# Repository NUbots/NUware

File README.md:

# NUware
Hardware used by the NUbots team.

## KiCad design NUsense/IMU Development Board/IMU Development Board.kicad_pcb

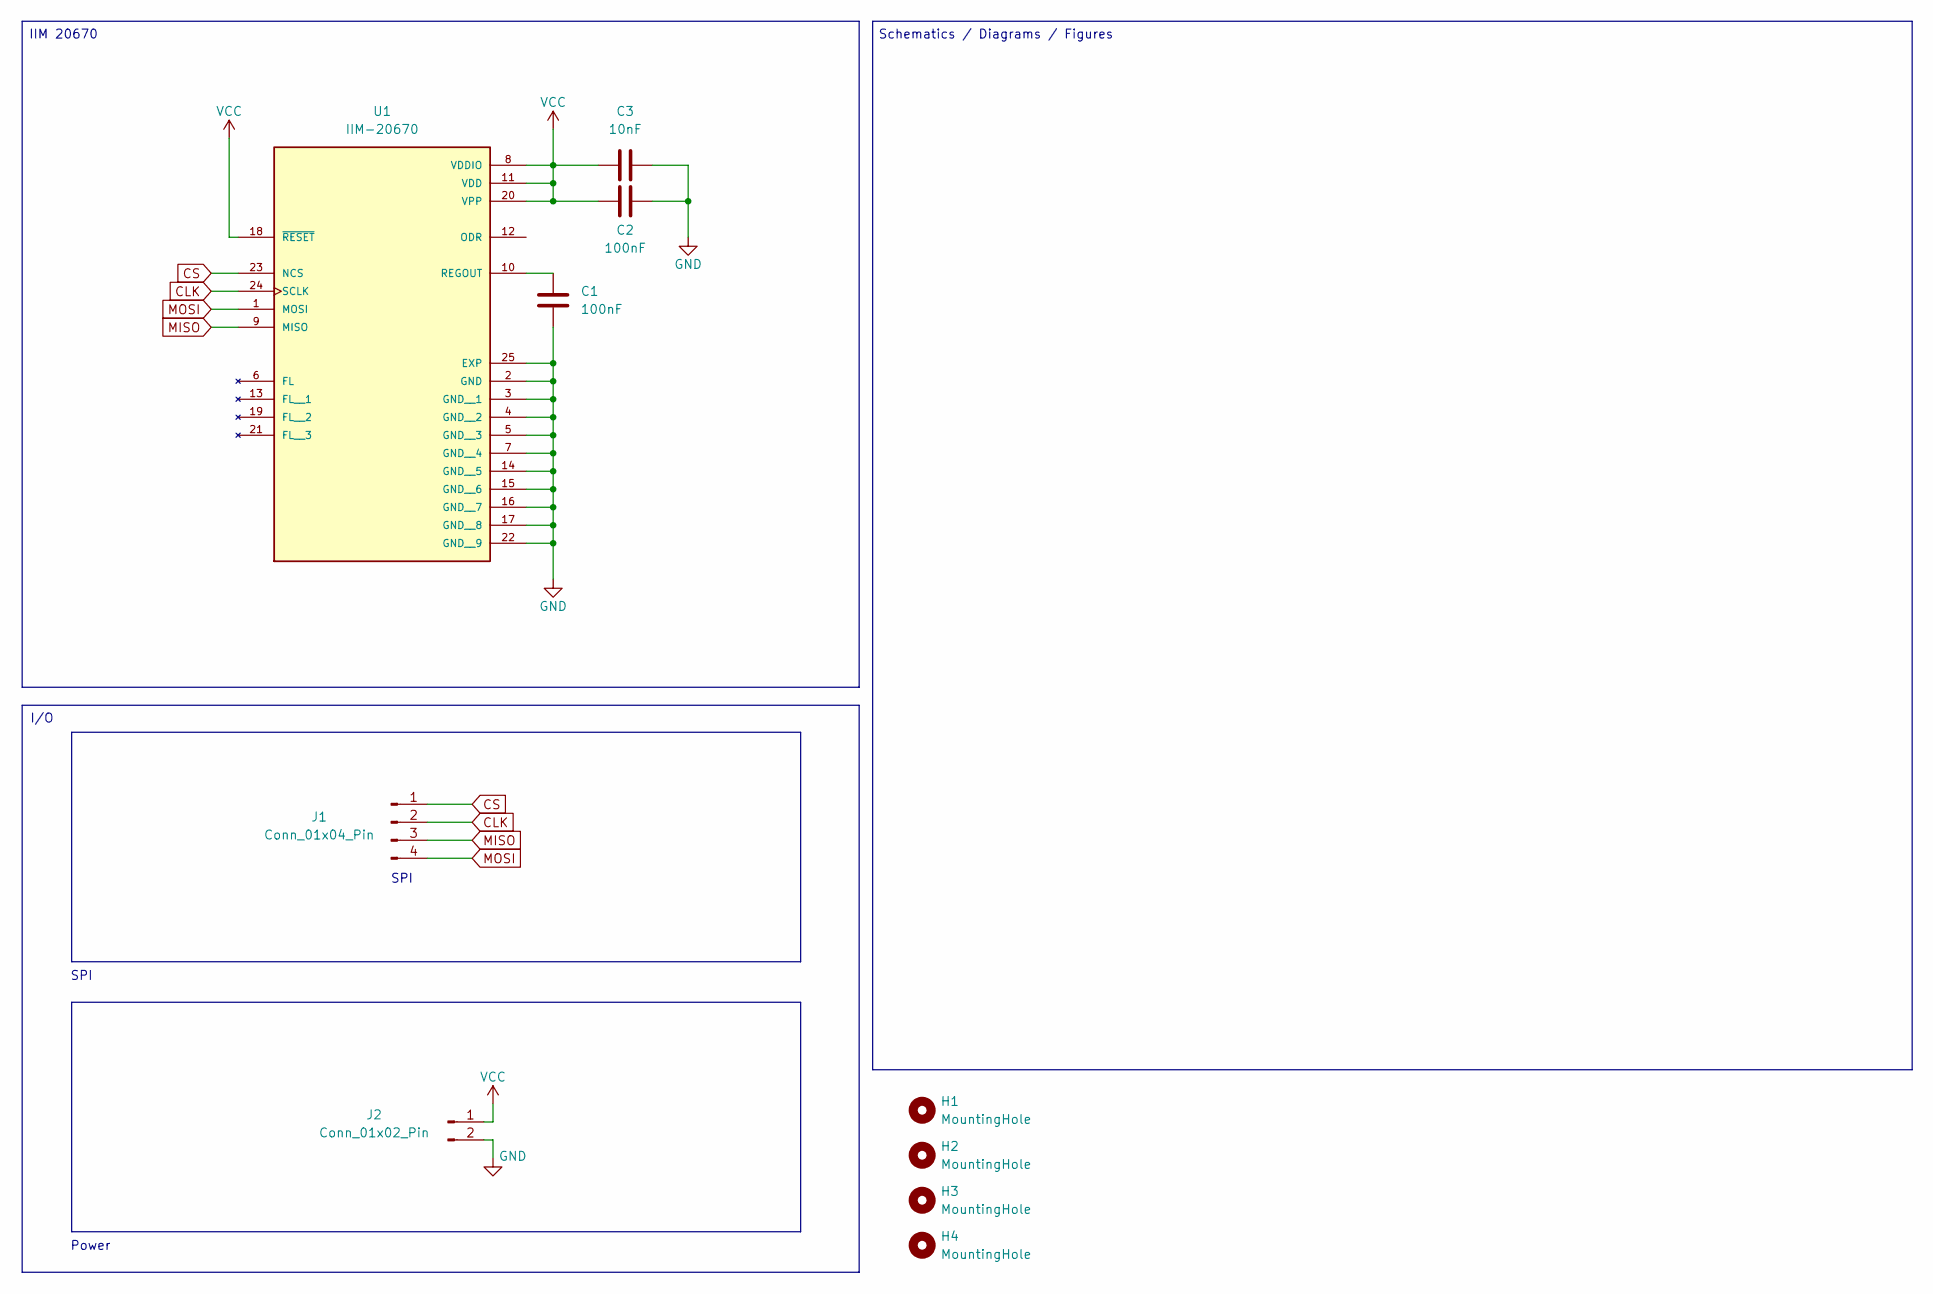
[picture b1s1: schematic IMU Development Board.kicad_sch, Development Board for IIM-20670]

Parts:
C1, C2: 100nF; C_1808_4520Metric_Pad1.72x2.30mm_HandSolder
C3: 10nF; C_1808_4520Metric_Pad1.72x2.30mm_HandSolder
H1, H2, H3, H4: MountingHole; MountingHole_4mm
J1: Conn_01x04_Pin; PinHeader_1x04_P2.54mm_Vertical_SMD_Pin1Left
J2: Conn_01x02_Pin; PinHeader_1x02_P2.54mm_Vertical_SMD_Pin1Left
U1: IIM-20670; QFN50P450X450X115-25N; PARTREV 1.1

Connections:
CLK: J1.2, U1.24 (SCLK)
CS: J1.1, U1.23 (NCS)
GND: C1.2, C2.1, C3.2, J2.2, U1.2 (GND), U1.3 (GND__1), U1.4 (GND__2), U1.5 (GND__3), U1.7 (GND__4), U1.14 (GND__5), U1.15 (GND__6), U1.16 (GND__7), U1.17 (GND__8), U1.22 (GND__9), U1.25 (EXP)
MISO: J1.3, U1.9 (MISO)
MOSI: J1.4, U1.1 (MOSI)
unnamed: C1.1, U1.10 (REGOUT)
VCC: C2.2, C3.1, J2.1, U1.8 (VDDIO), U1.11 (VDD), U1.18 (~RESET), U1.20 (VPP)

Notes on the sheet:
Power
IIM 20670
Schematics / Diagrams / Figures
I/O
SPI

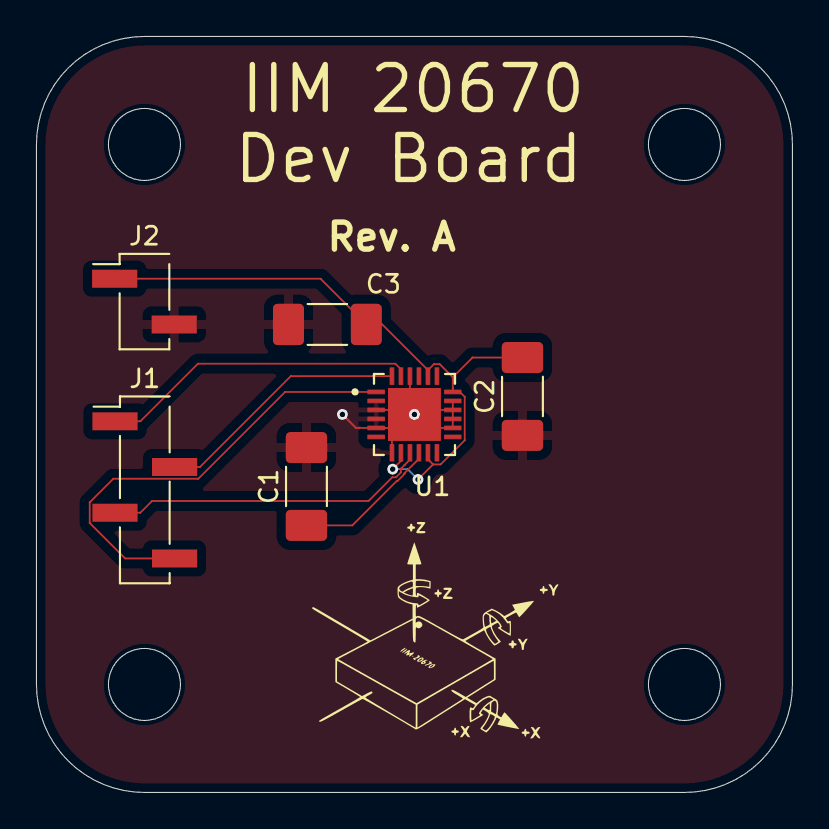
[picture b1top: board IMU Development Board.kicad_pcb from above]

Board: 2 copper layers, 42.0 x 42.0 mm, 10 parts (0 on the bottom side), 7 nets.

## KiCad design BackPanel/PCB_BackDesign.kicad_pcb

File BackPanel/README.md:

Back-Panel IO
=============

## Brief
Displays information through a series of LEDs including two RGB LEDs and takes inputs in from the user through three buttons; one of which shuts of power to the servos in case of an emergency. As a further convenience, there are two headers to power two fans with 12 V. The PCB is connected to the subcontroller through two cables.

## Motivation
The back-panel IO [originally designed by Robotis](https://github.com/ROBOTIS-GIT/ROBOTIS-OP-Series-Data/blob/master/ROBOTIS-OP%2C%20ROBOTIS-OP2/Hardware/Electronics/Boards/DARwIn-OP_Interface_rev3.pdf) was modified slightly for the NUgus to have 3D-printed buttons. These buttons floated between the PCB and the outer panel. As such, they were very finicky and sometimes got themselves stuck. Furthermore, given that the underlying electrical switch was a generic tactile momentary switch with a very short actuation depth, there was little tactile feedback. That is to say that there wasn't a very satsifying click which sometimes made the user doubt whether a contact was made. (This would compound separate but related issues with the reliability of the button firmware.) Another grievance was the fact that the mounting holes of the PCB were near the pads of the switches; if a metal washer was used, then it would short the switch.

## Resistors
The original design by Robotis had only 470 Ω resistors for all LEDs including the RGB ones. This seemed inconsistent; so, 240 Ω resistors were used for the green and blue LEDs since they often have higher forward voltages. Going off from [the datasheet](https://s3-us-west-2.amazonaws.com/catsy.557/Dialight_CBI_data_598-0603_Apr2018.pdf) for the Dialight 598 series, these resistors should give a current of 2.5 mA in each LED and roughly a forward voltage of 2 V for the red and yellow-green LEDs, 2.6 V for the blue LED, and 2.75 V for the green LED.

## Switch
[The KS11R2xCQD](https://www.ckswitches.com/media/1342/ks.pdf) was chosen as the replacement switch since it had a longer travel of 0.71 mm, had shorter profile than similar alternatives, and was relatively cheaper.

An alternative for future revisions is [the 5501M series](https://sten-eswitch-13110800-production.s3.amazonaws.com/system/asset/product_line/data_sheet/24/5500.pdf) which has a longer travel of about 1 mm -- the datasheet is somewhat ambiguous. It can even have an embedded LED which can be wired to the second arm of a SPDT -- labelled NC in the datasheet -- and can be used to signify when the button is pressed as a form of visual feedback. However, compared to the KS11R2xCQD, it has a much taller profile which would mean that the PCB would need to be recessed further back into the torso.

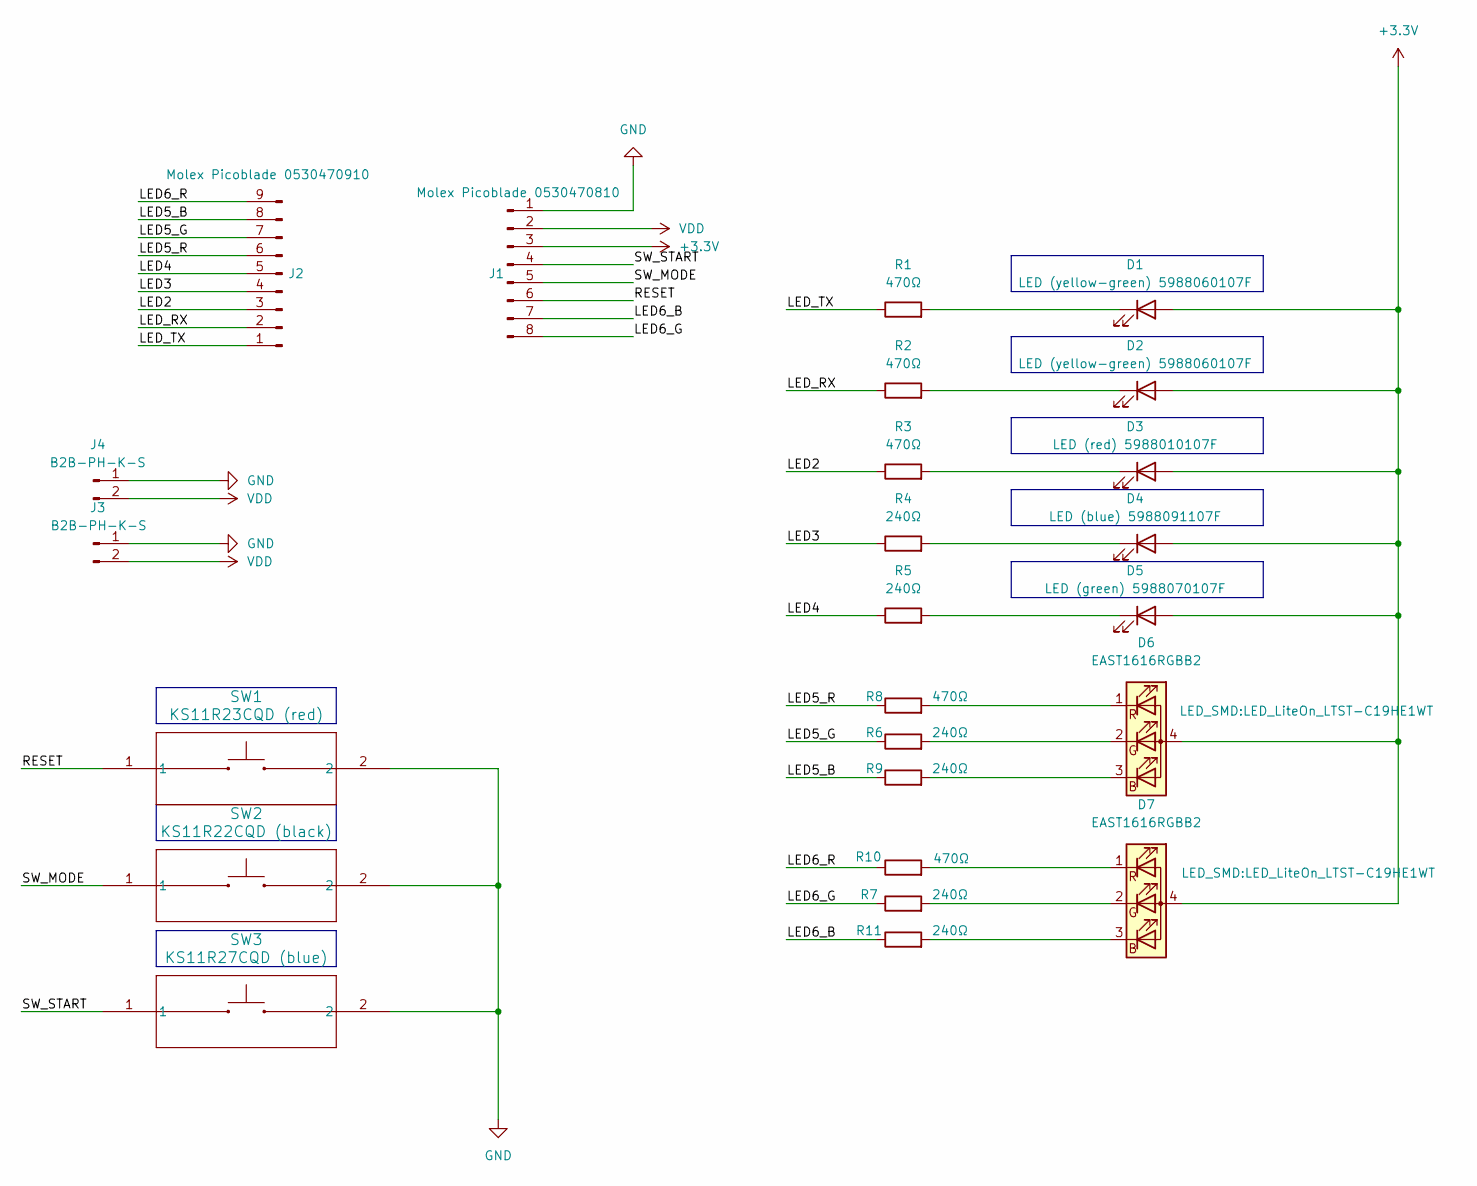
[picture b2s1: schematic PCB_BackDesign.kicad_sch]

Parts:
D1, D2: LED (yellow-green) 5988060107F; LED_0603_1608Metric
D3: LED (red) 5988010107F; LED_0603_1608Metric
D4: LED (blue) 5988091107F; LED_0603_1608Metric
D5: LED (green) 5988070107F; LED_0603_1608Metric
D6, D7: EAST1616RGBB2; LED_LiteOn_LTST-C19HE1WT
J1: Molex Picoblade 0530470810; Molex_PicoBlade_53047-0810_1x08_P1.25mm_Vertical
J2: Molex Picoblade 0530470910; Molex_PicoBlade_53047-0910_1x09_P1.25mm_Vertical
J3, J4: B2B-PH-K-S; JST_PH_B2B-PH-K_1x02_P2.00mm_Vertical
R1, R2, R3, R8, R10: 470Ω; R_0603_1608Metric
R4, R5, R6, R7, R9, R11: 240Ω; R_0603_1608Metric
SW1: KS11R23CQD (red); KS11_CNK
SW2: KS11R22CQD (black); KS11_CNK
SW3: KS11R27CQD (blue); KS11_CNK

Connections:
+3.3V: D1.2 (A), D2.2 (A), D3.2 (A), D4.2 (A), D5.2 (A), D6.4 (A), D7.4 (A), J1.3
/LED2: J2.3, R3.1
/LED3: J2.4, R4.1
/LED4: J2.5, R5.1
/LED5_B: J2.8, R9.1
/LED5_G: J2.7, R6.1
/LED5_R: J2.6, R8.1
/LED6_B: J1.7, R11.1
/LED6_G: J1.8, R7.1
/LED6_R: J2.9, R10.1
/LED_RX: J2.2, R2.1
/LED_TX: J2.1, R1.1
/RESET: J1.6, SW1.1; also elsewhere on the board
/SW_MODE: J1.5, SW2.1; also elsewhere on the board
/SW_START: J1.4, SW3.1; also elsewhere on the board
GND: J1.1, J3.1, J4.1, SW1.2, SW2.2, SW3.2; also elsewhere on the board
unnamed: D1.1 (K), R1.2
unnamed: D2.1 (K), R2.2
unnamed: D3.1 (K), R3.2
unnamed: D4.1 (K), R4.2
unnamed: D5.1 (K), R5.2
unnamed: D6.3 (BK), R9.2
unnamed: D6.2 (GK), R6.2
unnamed: D6.1 (RK), R8.2
unnamed: D7.3 (BK), R11.2
unnamed: D7.2 (GK), R7.2
unnamed: D7.1 (RK), R10.2
VDD: J1.2, J3.2, J4.2

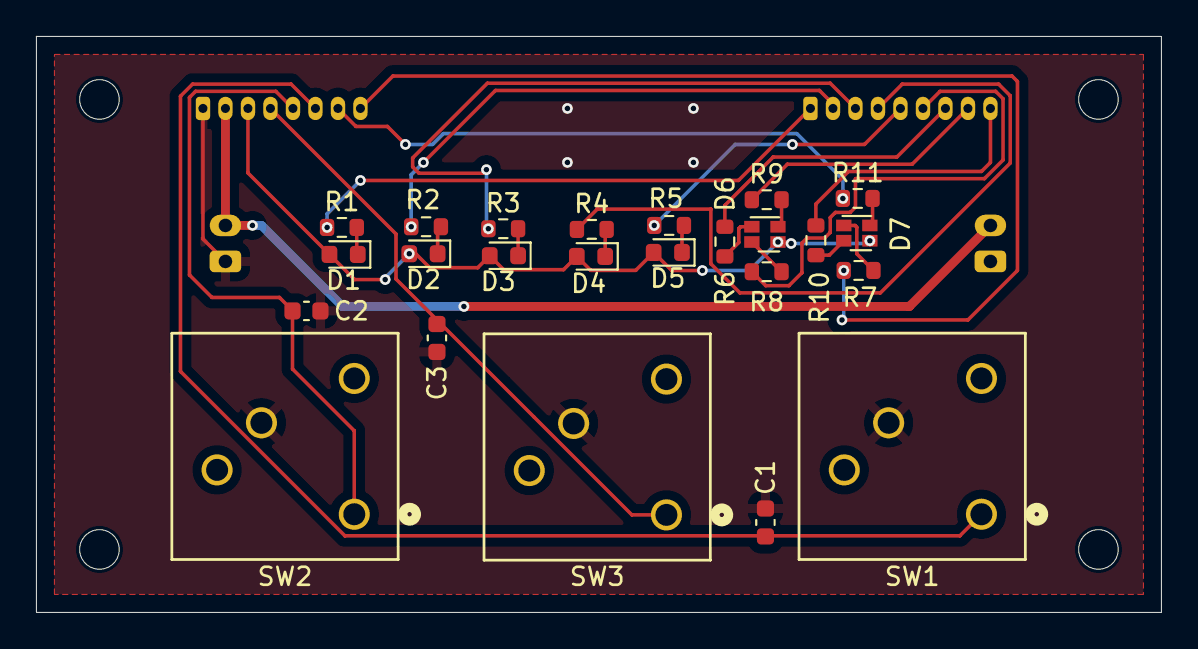
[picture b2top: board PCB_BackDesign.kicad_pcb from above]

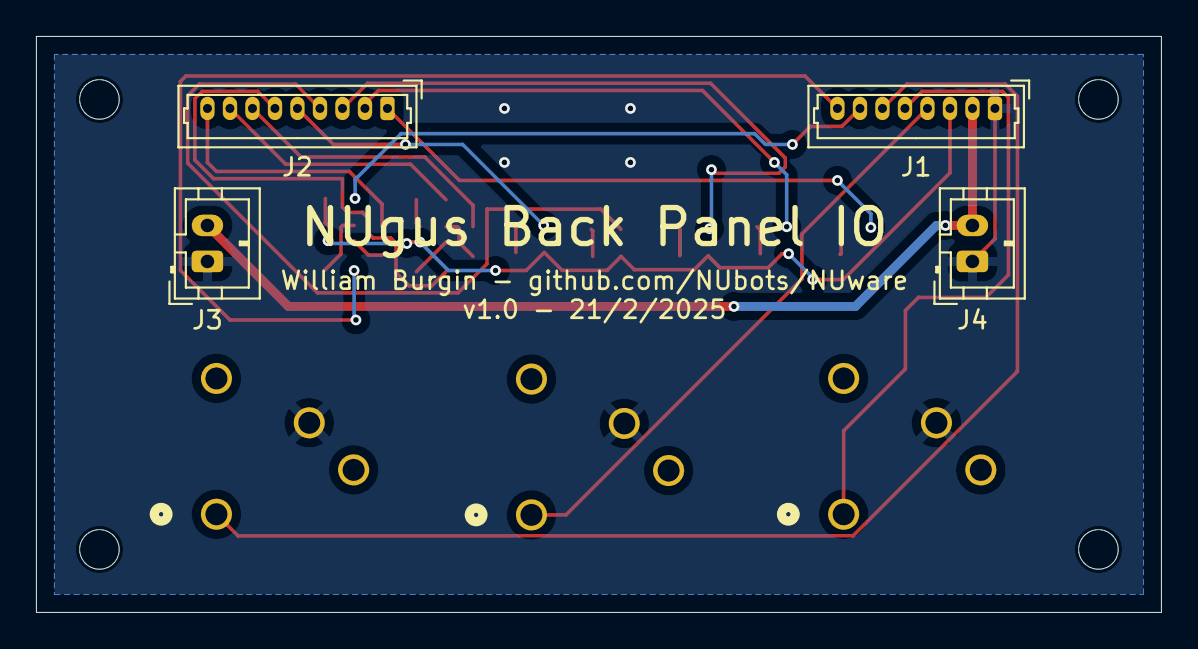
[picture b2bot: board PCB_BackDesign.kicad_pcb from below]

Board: 2 copper layers, 62.5 x 32.0 mm, 28 parts (4 on the bottom side), 28 nets.

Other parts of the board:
C1, C2, C3: 100nF; C_0603_1608Metric

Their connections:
/RESET: C1.1; also elsewhere on the board
/SW_MODE: C2.1; also elsewhere on the board
/SW_START: C3.1; also elsewhere on the board
GND: C1.2, C2.2, C3.2; also elsewhere on the board

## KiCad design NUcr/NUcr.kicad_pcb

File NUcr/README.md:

NUcr
====

## Motivation
The bare OpenCR 1.0 board did not have enough headers nor the right headers for the then existing cabling that was used for the CM740. For example, the OpenCR only has three JST B4B-EH-A headers for the RS485 Dynamixel bus.

## Description
This Arduino-like shield effectively emulated the headers found on the CM740 as well as a few other conveniences like a connection for a standalone RS485 serial converter and headers for 12 V fans.

It has:
* nine Molex Spox 22-03-5045 headers -- three of which connect to the OpenCR's three JST headers --,
* one Molex Picoblade 53047-0810 header and one 53047-0910 header for the button panel,
* four JST B2B-PH-K-S headers for the fans -- one of which connects to the OpenCR's 12 V header --,
* an Arduino footprint -- this only serves to connect 3.3 V and to provide structural connection --,
* and lastly one three-pin header for a standalone RS485 serial converter.

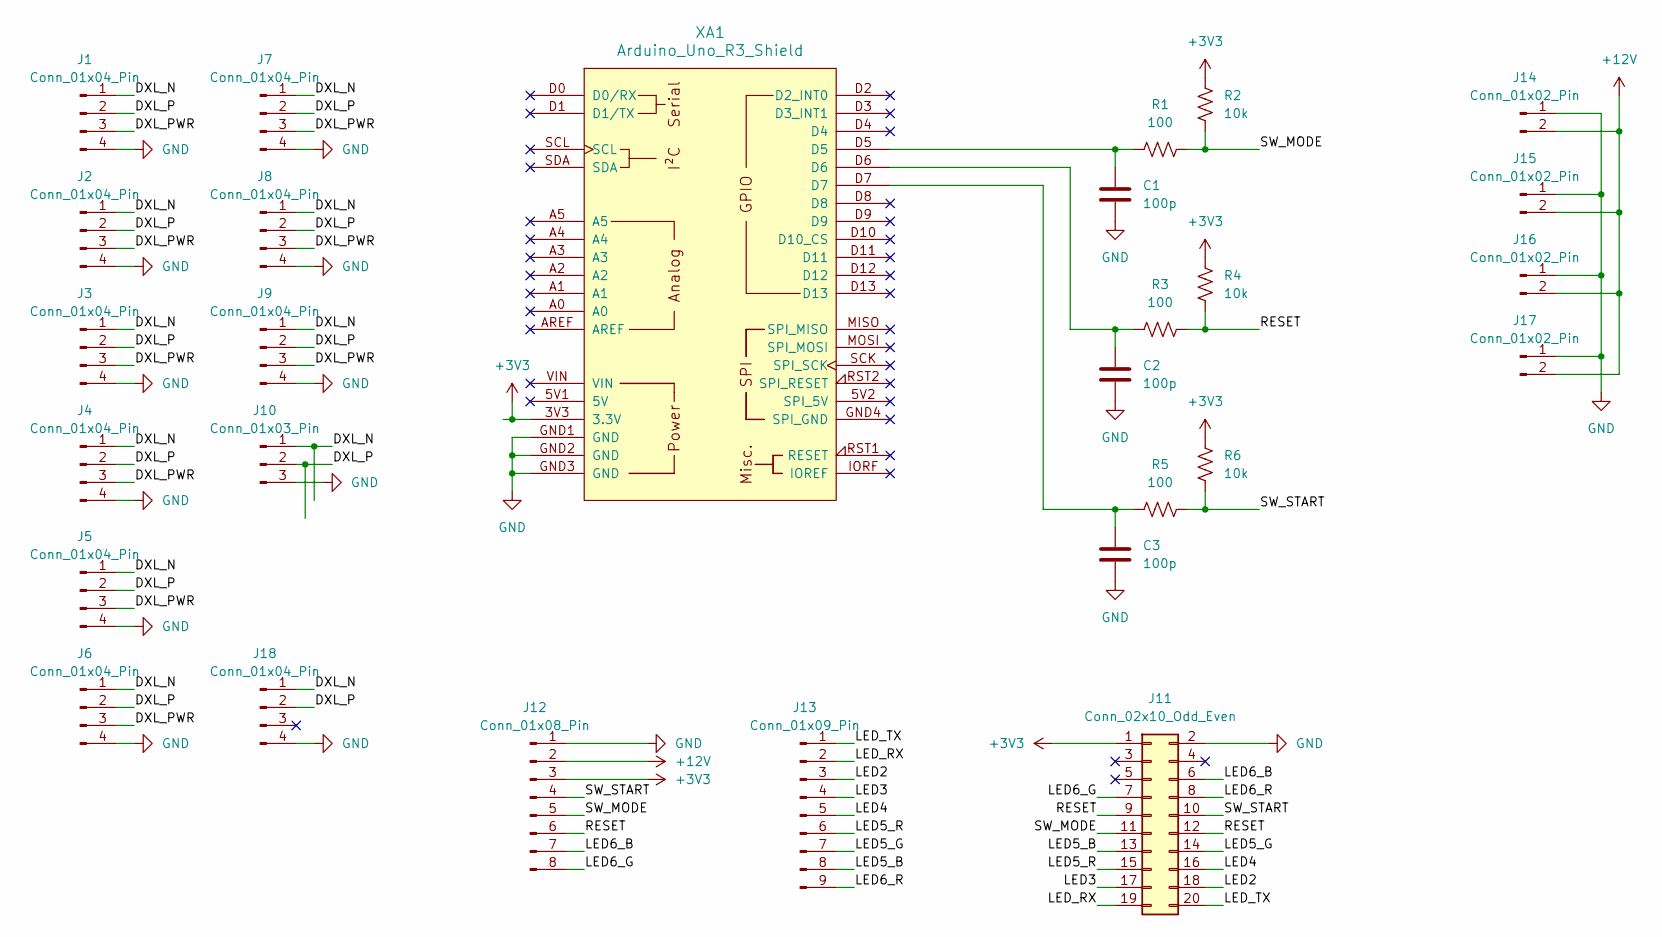
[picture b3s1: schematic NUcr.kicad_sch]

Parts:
C1, C2, C3: 100p; C_0603_1608Metric
J1, J2, J3, J4, J5, J6, J7, J8, J9: Conn_01x04_Pin; Molex_SPOX_5267-04A_1x04_P2.50mm_Vertical
J10: Conn_01x03_Pin; PinHeader_1x03_P2.54mm_Vertical
J11: Conn_02x10_Odd_Even; PinSocket_2x10_P2.54mm_Vertical
J12: Conn_01x08_Pin; Molex_PicoBlade_53047-0810_1x08_P1.25mm_Vertical
J13: Conn_01x09_Pin; Molex_PicoBlade_53047-0910_1x09_P1.25mm_Vertical
J14, J15, J16, J17: Conn_01x02_Pin; JST_PH_B2B-PH-K_1x02_P2.00mm_Vertical
J18: Conn_01x04_Pin; PinHeader_1x04_P2.54mm_Vertical
R1, R3, R5: 100; R_0603_1608Metric
R2, R4, R6: 10k; R_0603_1608Metric
XA1: Arduino_Uno_R3_Shield

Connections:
+3V3: J11.1, J12.3, R2.1, R4.1, R6.1, XA1.3V3 (3.3V)
+12V: J12.2, J14.2, J15.2, J16.2, J17.2
/DXL_N: J1.1, J2.1, J3.1, J4.1, J5.1, J6.1, J7.1, J8.1, J9.1, J10.1, J18.1
/DXL_P: J1.2, J2.2, J3.2, J4.2, J5.2, J6.2, J7.2, J8.2, J9.2, J10.2, J18.2
/DXL_PWR: J1.3, J2.3, J3.3, J4.3, J5.3, J6.3, J7.3, J8.3, J9.3
/LED2: J11.18, J13.3
/LED3: J11.17, J13.4
/LED4: J11.16, J13.5
/LED5_B: J11.13, J13.8
/LED5_G: J11.14, J13.7
/LED5_R: J11.15, J13.6
/LED6_B: J11.6, J12.7
/LED6_G: J11.7, J12.8
/LED6_R: J11.8, J13.9
/LED_RX: J11.19, J13.2
/LED_TX: J11.20, J13.1
/RESET: J11.9, J11.12, J12.6, R3.2, R4.2
/SW_MODE: J11.11, J12.5, R1.2, R2.2
/SW_START: J11.10, J12.4, R5.2, R6.2
GND: C1.2, C2.2, C3.2, J1.4, J2.4, J3.4, J4.4, J5.4, J6.4, J7.4, J8.4, J9.4, J10.3, J11.2, J12.1, J14.1, J15.1, J16.1, J17.1, J18.4, XA1.GND1 (GND), XA1.GND2 (GND), XA1.GND3 (GND)
unnamed: C1.1, R1.1, XA1.D5
unnamed: C2.1, R3.1, XA1.D6
unnamed: C3.1, R5.1, XA1.D7

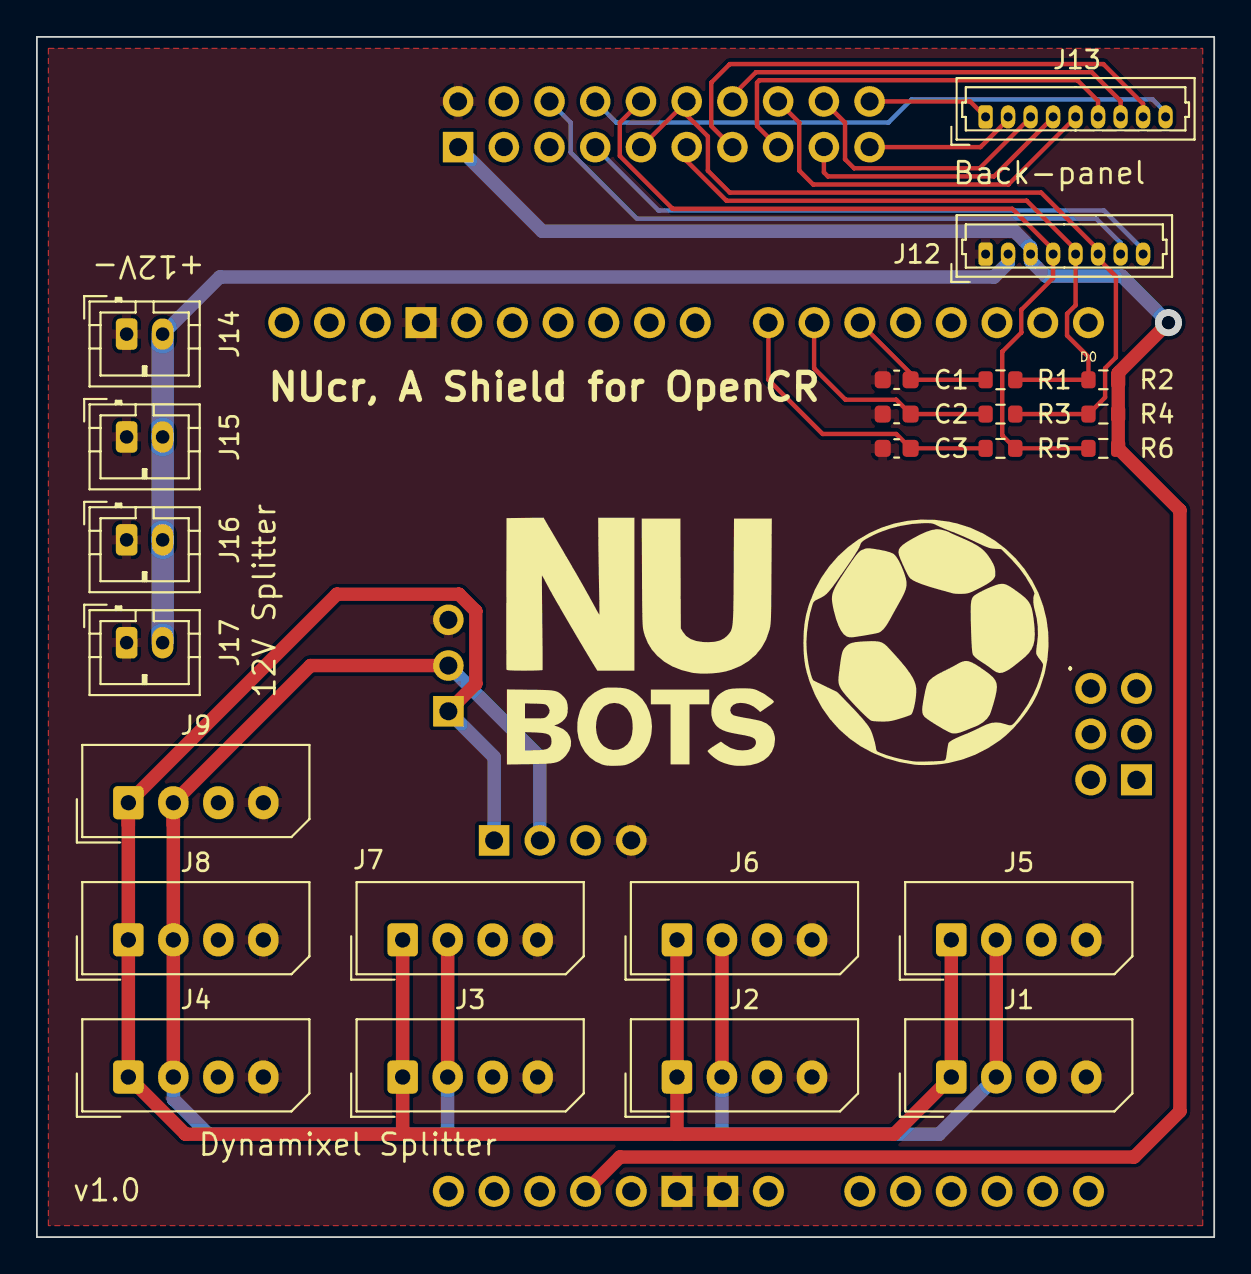
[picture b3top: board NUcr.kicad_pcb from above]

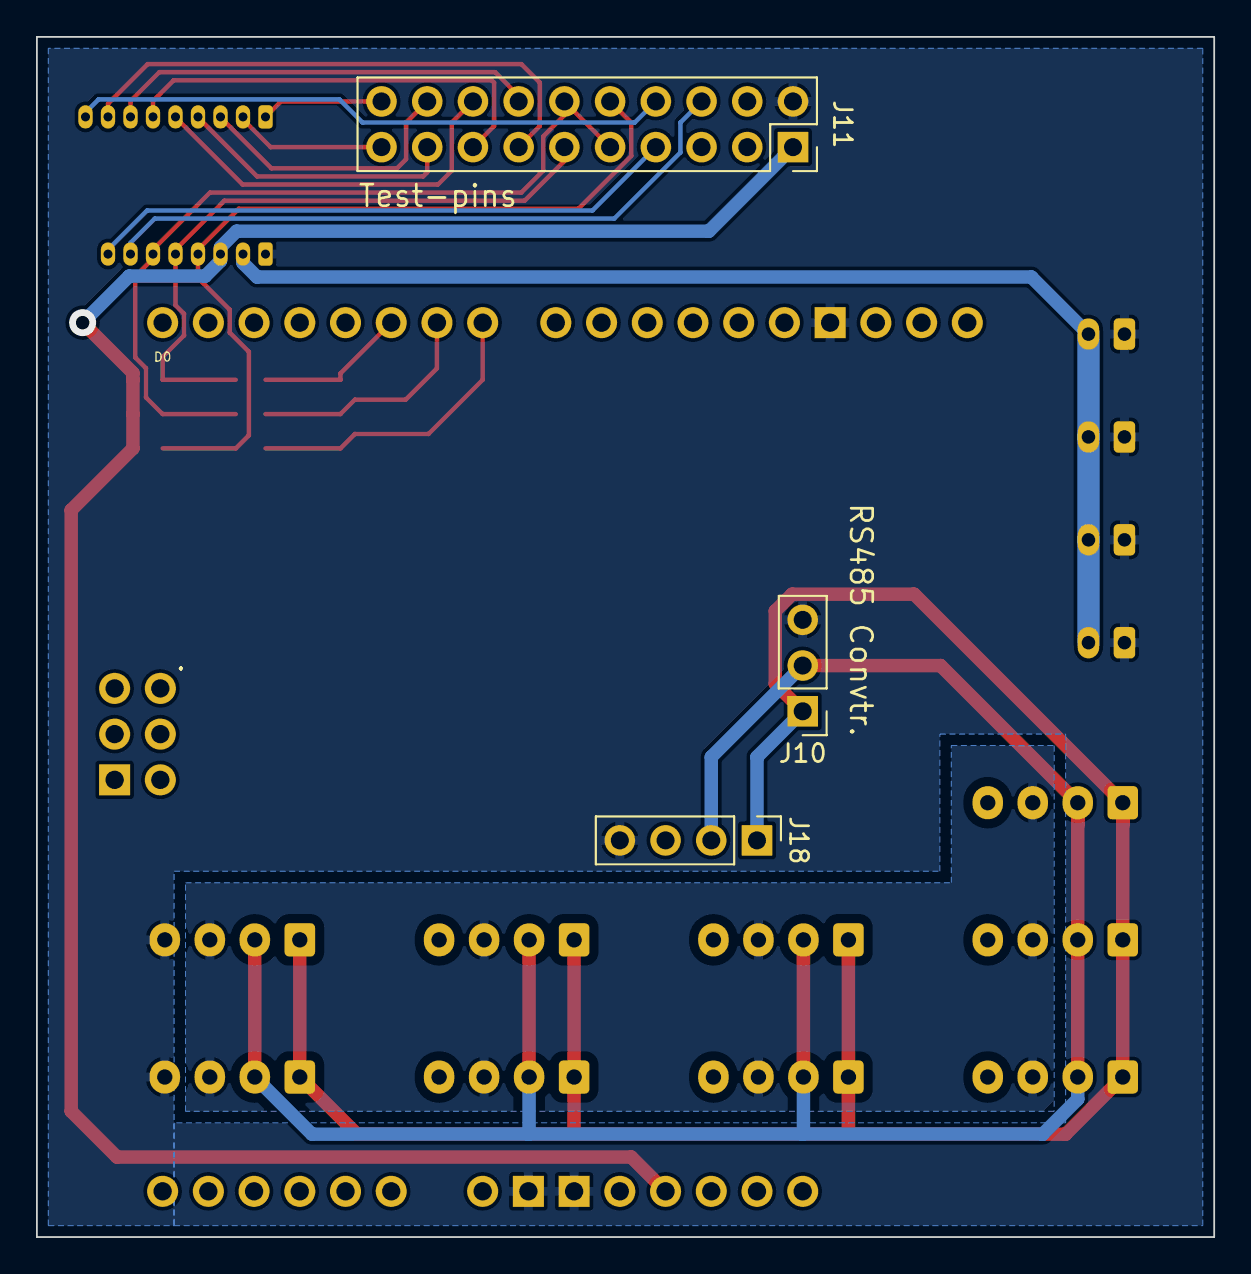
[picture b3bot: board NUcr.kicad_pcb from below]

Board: 2 copper layers, 65.4 x 66.7 mm, 28 parts (3 on the bottom side), 23 nets.

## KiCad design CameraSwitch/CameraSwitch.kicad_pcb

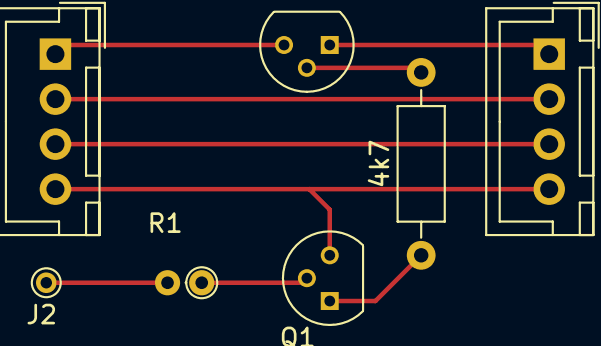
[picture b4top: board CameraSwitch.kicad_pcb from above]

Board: 2 copper layers, 7 parts (0 on the bottom side), 9 nets.

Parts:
4k7: R2; R_Axial_DIN0207_L6.3mm_D2.5mm_P10.16mm_Horizontal
J1: USB_IN; JST_XH_B04B-XH-A_04x2.50mm_Straight
J2: GPIO; PINTST
J3: USB_OUT; JST_XH_B04B-XH-A_04x2.50mm_Straight
Q1: BC547; TO-92_Molded_Narrow
Q2: BC327; TO-92_Molded_Narrow
R1: 10k; R_Axial_DIN0204_L3.6mm_D1.6mm_P1.90mm_Vertical

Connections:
/3V3: J2.1, R1.2
/5V_IN: J1.1, Q2.3
/5V_OUT: J3.1, Q2.1
/D+: J1.2, J3.2
/D-: J1.3, J3.3
Earth: J1.4, J3.4, Q1.3
unnamed: 4k7.1, Q1.1
unnamed: 4k7.2, Q2.2
unnamed: Q1.2, R1.1

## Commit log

2017-06-02 Cleans up formatting in README.md.
2017-06-02 Adds the USB Camera Switch kicad design files.
2017-06-02 Adds the Power Board altium design files.
2017-06-25 Igus design files
2017-06-26 Rearranged files and added a readme for the igus files.
2017-07-19 Adds license
2018-01-25 Create A
2018-01-29 Update NUsense Files
2018-01-30 Ignore backup files
2018-01-30 Change hierarchy layout
2018-01-30 Add power components
2018-01-30 Update Component Values
2018-01-31 Correct broken files
2018-01-31 Add files
2018-01-31 Adds datasheets
2018-01-31 Main page additions
2018-01-31 Add datasheet
2018-01-31 Add datasheets
2018-01-31 Update connections
2018-02-01 Footprints
2018-02-01 ESD protection
2018-02-02 Adds new schematic symbols
    AVRC5S and DXL_PWR
2018-02-02 Adds more datasheets
2018-02-02 Adds new footprints
2018-02-02 Adds annotations and footprints to all components
2018-02-02 Removes unneeded schematic
2018-02-02 Adds annotations and footprints
    Changes crystal selection
2018-02-02 Adds all 5 RS485 sheets
2018-02-02 Other changes that apparently are important....?
2018-02-02 More Changes
2018-02-02 Further Changes
2018-02-02 Buttons/LEDs
2018-02-02 Fan PWM
2018-02-02 Footprint Fan PWM
2018-02-03 Datasheets
2018-02-06 Add LED and Button
2018-02-06 Cleans up some minor things
2018-02-06 Further Cleaning
2018-02-06 RTC removed
2018-02-06 Add labels
2018-05-05 Convert KiCad files to Altium
2018-09-28 Decimate skins
2018-10-19 Update igus step files
2018-10-19 Don't look
2019-04-18 Updates 3d model files
2019-04-30 Removes duplicate files
2019-09-28 Add custom brackets and cable clamps
2019-09-28 Move new files to correct location
2019-09-28 Add knee servo cable holder
2019-11-25 Add NUFSR files
2019-12-04 Add igus extension
2021-01-03 Added STM32CubeMX Workspace files.
    Got UART transmission/receive coms working using Interrupts. In addition, the NUFRSR.ioc file has been updated to correctly match the NUfsr board schematics.
2021-01-07 Error checking & comment tidy for USART files
    Tidied code/comments and removed unused variables and includes.
2021-01-22 Updated .ioc configuration file & Defines for IMU.
    1. .ioc config file updates for SPI to IMU communication settings
    2. #define implemented for all IMU address commands
    3. Still need to implement data defines for IMU commands
2021-02-05 Changes to imu.h, and main.c for debugging
2021-02-28 Implemented IMU.c for custom functions. Added init settings.
    Implemented a source file the IMU. Created simple transfer functions that will help speed up further debugging.
2021-06-30 Add urdf files and first updated version of URDF
    TODO: Finish upper body
2021-06-30 Update upper body
    Still need to fix up more
    - Add correct physics
    - Add better mesh models
    - Better position visual mesh's
2021-07-19 STM32CubeIDE Files
    Added files for STM32CubeIDE Development
2022-03-01 STM 1.8.0 Update
    Updated STM32CubeIDE software
2022-03-01 Fix IOC Config
    Fixed:
    SPI Boardrate presale from 16-->256
    Changed DXL_N_Pin from PP to OD
2022-04-13 IMU Test Code
    Added IMU Test Code
    Updated STM32 to 1.9, possible errors
2022-07-07 Added Config Report
2022-09-24 add all
2022-10-03 redeveloped IMU reader
2022-10-21 added new C++ project
2022-11-13 fixed the rs485 test code
2022-11-13 changed some things for the former commit
2022-11-15 added polling versions for the RS485 helper functions
2022-11-18 made uart flags volatile
2022-11-26 usart working but not who am I
    With help from Clayton
2022-12-03 changed to .cpp
2022-12-03 added a C-style IMU library for simple polling
2022-12-10 added conversion from raw data and offsets for the IMU
2022-12-16 made a class for RS485
2023-01-04 fixed the burst-read for the IMU and tidied some things up
2023-01-06 changed some names for tests
2023-01-18 configured DMA for UART, not working yet
2023-01-28 tidied a few things in RS485
2023-01-28 add a Port class based on some of Robotis' code to make things higher-level and easier for protocol-handling
2023-01-28 added a Port class based on some of Robotis' code to make things higher-level and easier for protocol-handling
2023-01-29 fixed the DMA for UART-transmission; also cleaned some stuff in the RS485 class and in usart.c
2023-02-18 redefined how one communicates with the motor; abandoned the Port class for now until a robust ring buffer is developed.
2023-02-18 removed the psuedo-namespaces for the test code segments
2023-02-20 fixed the detection of the idle-line for the RS485 so that the DMA can handle phantom bytes
2023-02-21 Initialise packet class (Not working, not tested)
2023-02-24 added some Dynamixel code for packetising; added namespaces and folders; added peek for the Port class; fixed some other things
2023-02-26 shelved all the test code into a separate file to keep main.cpp tidy
2023-02-26 fixed a bug where the state whether packet is ready is begun as true instead of false as it should have been
2023-02-27 made some functions const
2023-03-01 fixed a bug with the accumulative CRC during decoding
2023-03-01 fixed a bug where the size was incorrectly recalculated when the RX buffer made a complete DMA transfer
2023-03-01 added the packet-handler to main
2023-03-02 tested sync-read and sync-write on the packet-handler
2023-03-06 reorganised separate files for the generic packet and devices on the robot; added sync-read to the polling
2023-03-13 set up continuous asynchronous polling of twenty motors; moved the switching of the direction of the RS485 transceiver to the interrupt-callback; fixed the baudrate of UART6; modified flush_tx in the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
2023-04-05 changed the writing of the indirect registers from using sync-write to using write instead; invesitgated optimising the speed of the Dynamixel communications.
2023-04-19 Added torque-enable and hardware error status to the indirect registers.
2023-08-15 Rewrote most of the dynamixel firmware; imported code from HardwareIO; rewrote the PacketHandler class to be simpler; changed 'checksum' to 'crc' in the imported code from HardwareIO.
2023-09-01 Added a read-loop in main(); re-ordered some files under platform into a NUsense folder; added process_data() and associated conversions and maths from HardwareIO; fixed the templated write-function 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
2023-09-19 Added a class for the NUsense communications called NUsenseIO to wrap most of the code; reformatted whitespace, tabs, etc., and reworded comments.
2024-01-30 DMA, TIM additions with LEDS
2024-03-03 All ports working with DMA
2024-04-30 Includes RS485 and testing
    *Not working fully, requires debugging
2024-05-04 Removed ADC FSR Bug
    Now can work for sending FSR Measurments
2024-06-03 Added files for the adapter; made a new folder for ephemeral boards.
2024-08-06 Adds files for x-series leg upgrade
    Files for the hip/ankle blocks and knee servos. These files also do away with the stock x-series idle wheel in favour of the MX style bolted wheel.
2024-08-06 Add stl files for x series legs
    This assembly also does away with the stock x-series idle wheel in favour of the MX style bolted wheel.
2024-08-14 port and added changes, cycles, adc
2024-08-14 Recieve Testing
2024-08-20 FSR ADC Working
2024-08-24 Ping, Global Ping and Read Command Firmware Working
2024-10-11 Fixed bug Ring Buffer, Circular DMA
2025-02-25 Redesigned the PCB for the back-panel IO.
2025-03-04 Add gitignore.
2025-03-04 Made a folder for ephemeral production files, e.g. gerbers.
2025-03-04 Add .gitignore.
2025-03-04 Add files.
2025-03-04 Fixed gitignore.
2025-03-04 Made the gitignore more consistent.
2025-03-04 Widened the gitignore's scope.
2025-03-04 I don't know what this is.
2025-03-05 Widen the gitignore's scope.
2025-03-05 First commit.
2025-03-05 Added documentation.
2025-03-06 Tidied up some designators; moved two traces on the top layer to pass
    DRC.
2025-03-07 Add further documentation.
2025-03-07 Added colours to the schematic.
2025-03-10 Fixed the imported switch component.
2025-03-11 Added a readme file; added part numbers to the schematic.
2025-03-11 Added three debouncing capacitors.
2025-03-12 Generated Gerber files for JLCPCB.
2025-03-13 copied IMU from nusense
2025-03-13 Latest imu testing, not working
2025-03-13 Added PDFs for easy reading on the GitHub website.
2025-03-13 Added screenshots and a BoM from DigiKey.
2025-03-18 Add the NUcr files for posterity. (#5)
    * First commit.
    * Added documentation.
    * Add further documentation.
2025-03-21 I really must stop making more commits.
2025-03-21 Readded the mounting holes which mysteriously went missing;
    updated the project to KiCAD 9.0 because I am silly.
2025-03-21 I hope that this is the last one.
2025-04-24 Redesign of Back Panel I/O PCB (#6)
    * Redesigned the PCB for the back-panel IO.
    * Made the gitignore more consistent.
    * Widened the gitignore's scope.
    * I don't know what this is.
    * Tidied up some designators; moved two traces on the top layer to pass
    DRC.
2025-11-28 New ICM 20670 Development Board
2025-12-08 Too long ago to remember.
2026-05-31 Added the gerbers for this PCB
2026-06-12 Added the gerbers for this PCB (#7)
